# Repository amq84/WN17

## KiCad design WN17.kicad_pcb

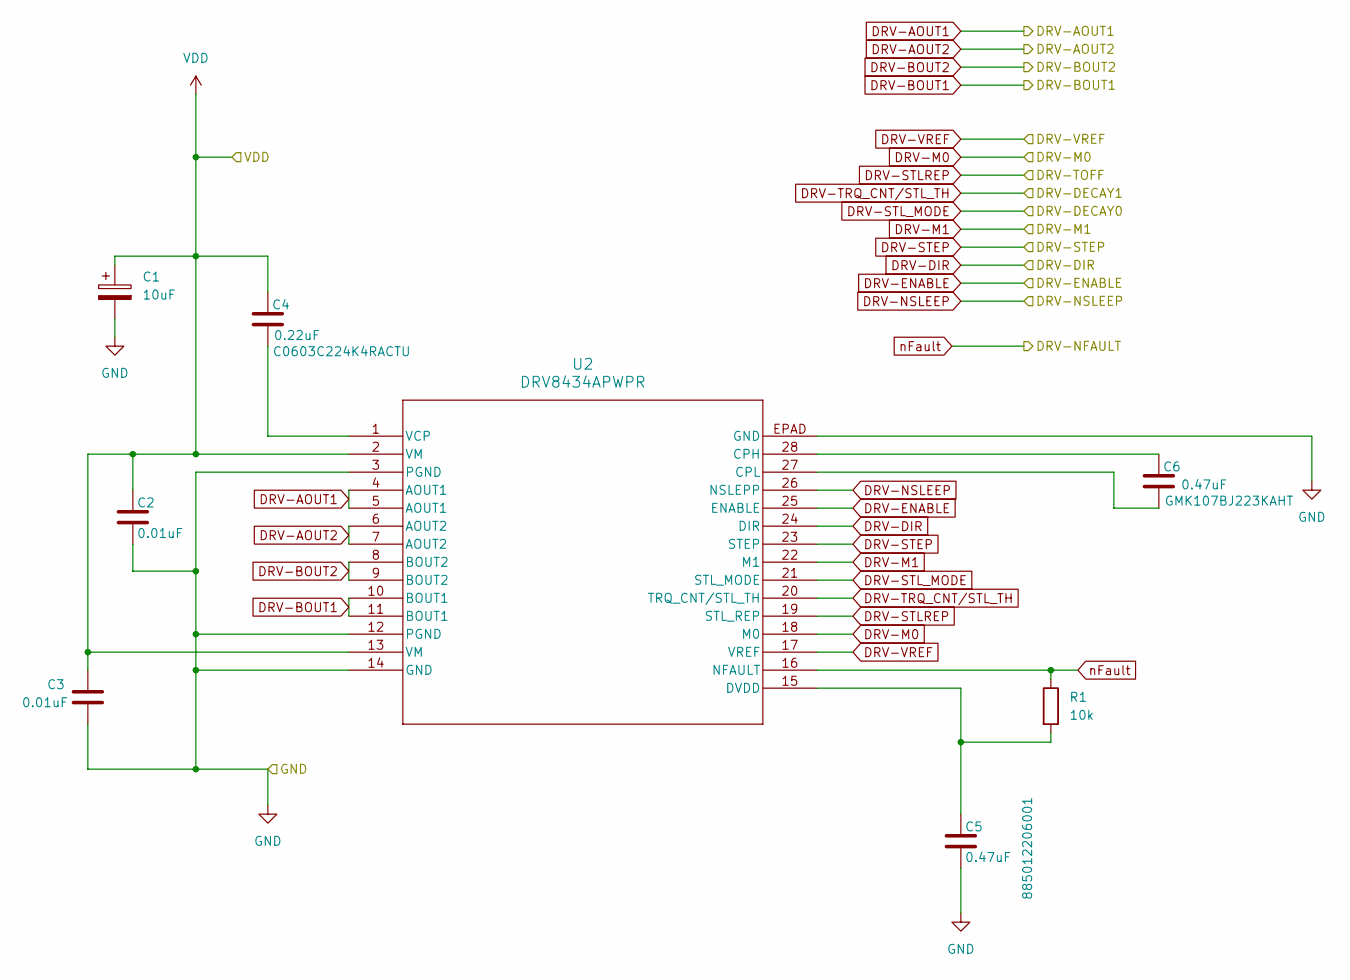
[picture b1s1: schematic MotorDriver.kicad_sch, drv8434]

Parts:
C1: 10uF; CP_Radial_D5.0mm_P2.50mm
C2, C3: 0.01uF; C_0603_1608Metric_Pad1.08x0.95mm_HandSolder
C4: 0.22uF; C_0603_1608Metric_Pad1.08x0.95mm_HandSolder
C5, C6: 0.47uF; C_0603_1608Metric_Pad1.08x0.95mm_HandSolder
R1: 10k; R_0603_1608Metric_Pad0.98x0.95mm_HandSolder
U2: DRV8434APWPR; DRV8434APWPR_TEX

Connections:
DRV-AOUT1: U2.4 (AOUT1), U2.5 (AOUT1); also elsewhere on the board
DRV-AOUT2: U2.6 (AOUT2), U2.7 (AOUT2); also elsewhere on the board
DRV-BOUT1: U2.10 (BOUT1), U2.11 (BOUT1); also elsewhere on the board
DRV-BOUT2: U2.8 (BOUT2), U2.9 (BOUT2); also elsewhere on the board
DRV-DIR: U2.24 (DIR); also elsewhere on the board
DRV-ENABLE: U2.25 (ENABLE); also elsewhere on the board
DRV-M0: U2.18 (M0); also elsewhere on the board
DRV-M1: U2.22 (M1); also elsewhere on the board
DRV-NSLEEP: U2.26 (NSLEPP); also elsewhere on the board
DRV-STEP: U2.23 (STEP); also elsewhere on the board
DRV-STLREP: U2.19 (STL_REP)
DRV-STL_MODE: U2.21 (STL_MODE)
DRV-TRQ_CNT/STL_TH: U2.20 (TRQ_CNT/STL_TH)
DRV-VREF: U2.17 (VREF); also elsewhere on the board
GND: C1.2, C2.2, C3.2, C5.2, U2.3 (PGND), U2.12 (PGND), U2.14 (GND), U2.EPAD (GND); also elsewhere on the board
unnamed: C6.1, U2.28 (CPH)
unnamed: C6.2, U2.27 (CPL)
unnamed: C5.1, R1.2, U2.15 (DVDD)
unnamed: C4.2, U2.1 (VCP)
VDD: C1.1, C2.1, C3.1, C4.1, U2.2 (VM), U2.13 (VM); also elsewhere on the board
nFault: R1.1, U2.16 (NFAULT); also elsewhere on the board

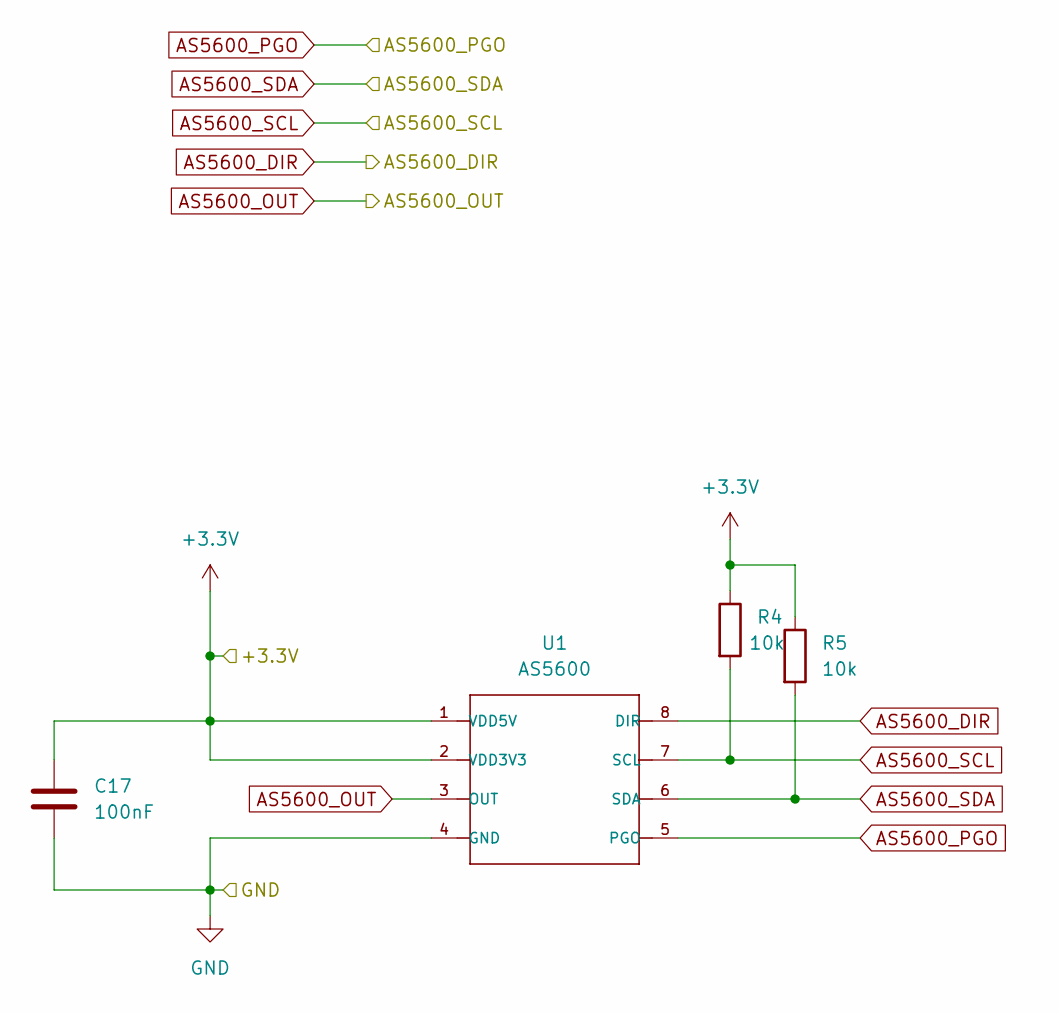
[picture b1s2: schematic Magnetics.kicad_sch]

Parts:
C17: 100nF; C_0603_1608Metric_Pad1.08x0.95mm_HandSolder
R4, R5: 10k; R_0603_1608Metric_Pad0.98x0.95mm_HandSolder
U1: AS5600

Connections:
+3.3V: C17.1, R4.1, R5.1, U1.1 (VDD5V), U1.2 (VDD3V3); also elsewhere on the board
AS5600_DIR: U1.8 (DIR); also elsewhere on the board
AS5600_OUT: U1.3 (OUT); also elsewhere on the board
AS5600_PGO: U1.5 (PGO); also elsewhere on the board
AS5600_SCL: R4.2, U1.7 (SCL); also elsewhere on the board
AS5600_SDA: R5.2, U1.6 (SDA); also elsewhere on the board
GND: C17.2, U1.4 (GND); also elsewhere on the board

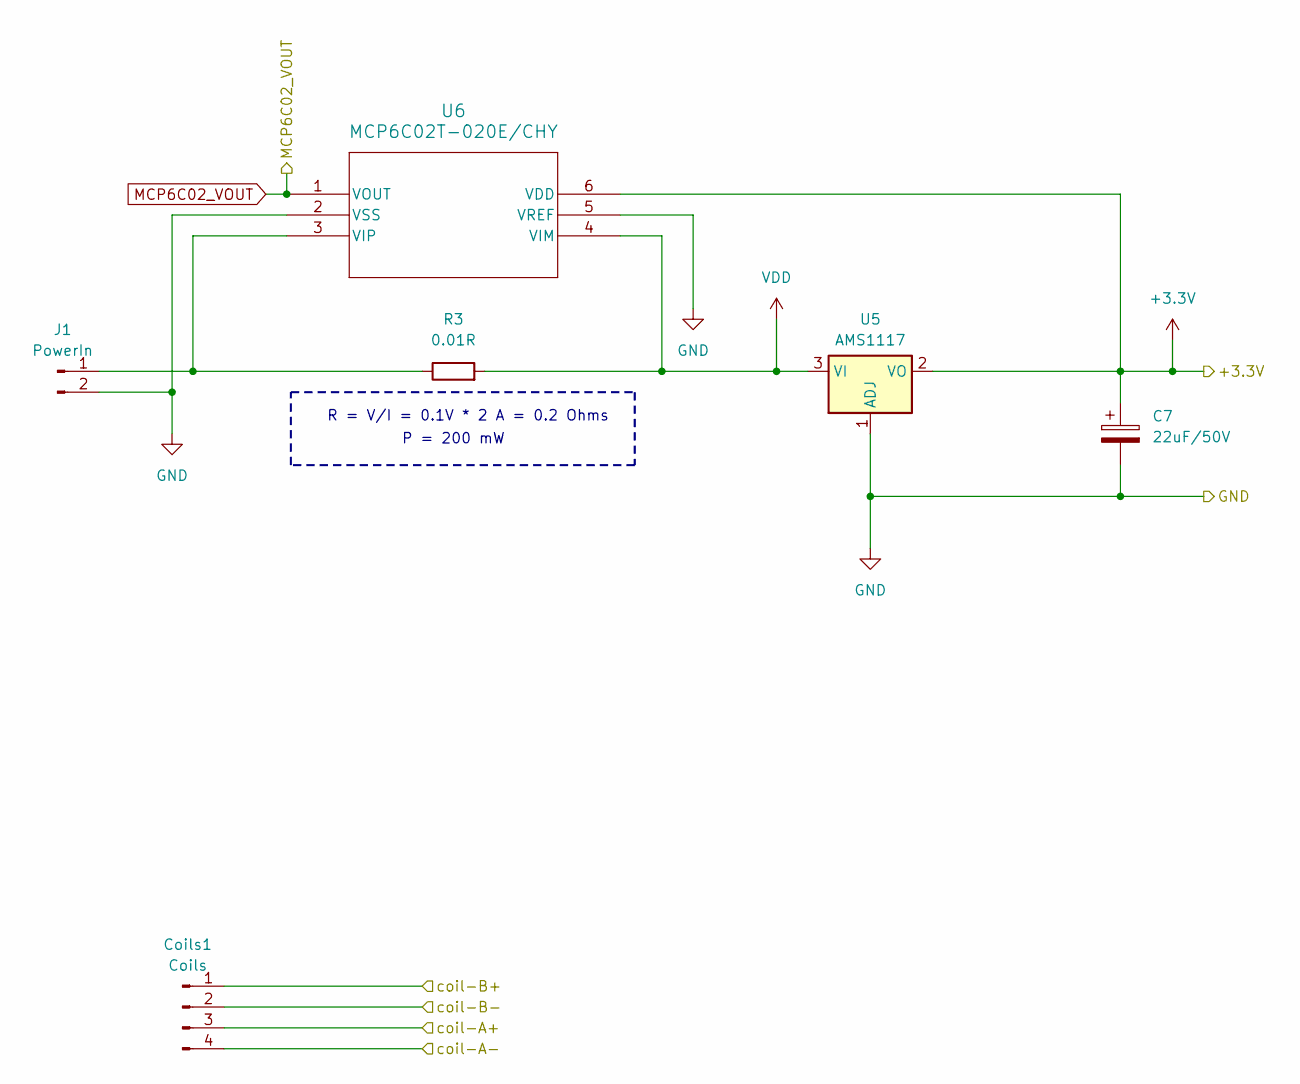
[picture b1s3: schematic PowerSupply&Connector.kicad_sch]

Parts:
C7: 22uF/50V; CP_Radial_D5.0mm_P2.50mm
Coils1: Coils; PinHeader_1x04_P2.54mm_Vertical
J1: PowerIn; PinHeader_1x02_P2.54mm_Vertical
R3: 0.01R; R_1206_3216Metric_Pad1.30x1.75mm_HandSolder
U5: AMS1117; SOT-223-3_TabPin2
U6: MCP6C02T-020E/CHY; SOT-23-6_CHY_MCH

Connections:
+3.3V: C7.1, U5.2 (VO), U6.6 (VDD); also elsewhere on the board
DRV-AOUT1: Coils1.4; also elsewhere on the board
DRV-AOUT2: Coils1.3; also elsewhere on the board
DRV-BOUT1: Coils1.1; also elsewhere on the board
DRV-BOUT2: Coils1.2; also elsewhere on the board
GND: C7.2, J1.2, U5.1 (ADJ), U6.2 (VSS), U6.5 (VREF); also elsewhere on the board
MCP6C02_VOUT: U6.1 (VOUT); also elsewhere on the board
unnamed: J1.1, R3.1, U6.3 (VIP)
VDD: R3.2, U5.3 (VI), U6.4 (VIM); also elsewhere on the board

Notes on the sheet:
R = V/I = 0.1V * 2 A = 0.2 Ohms
P = 200 mW

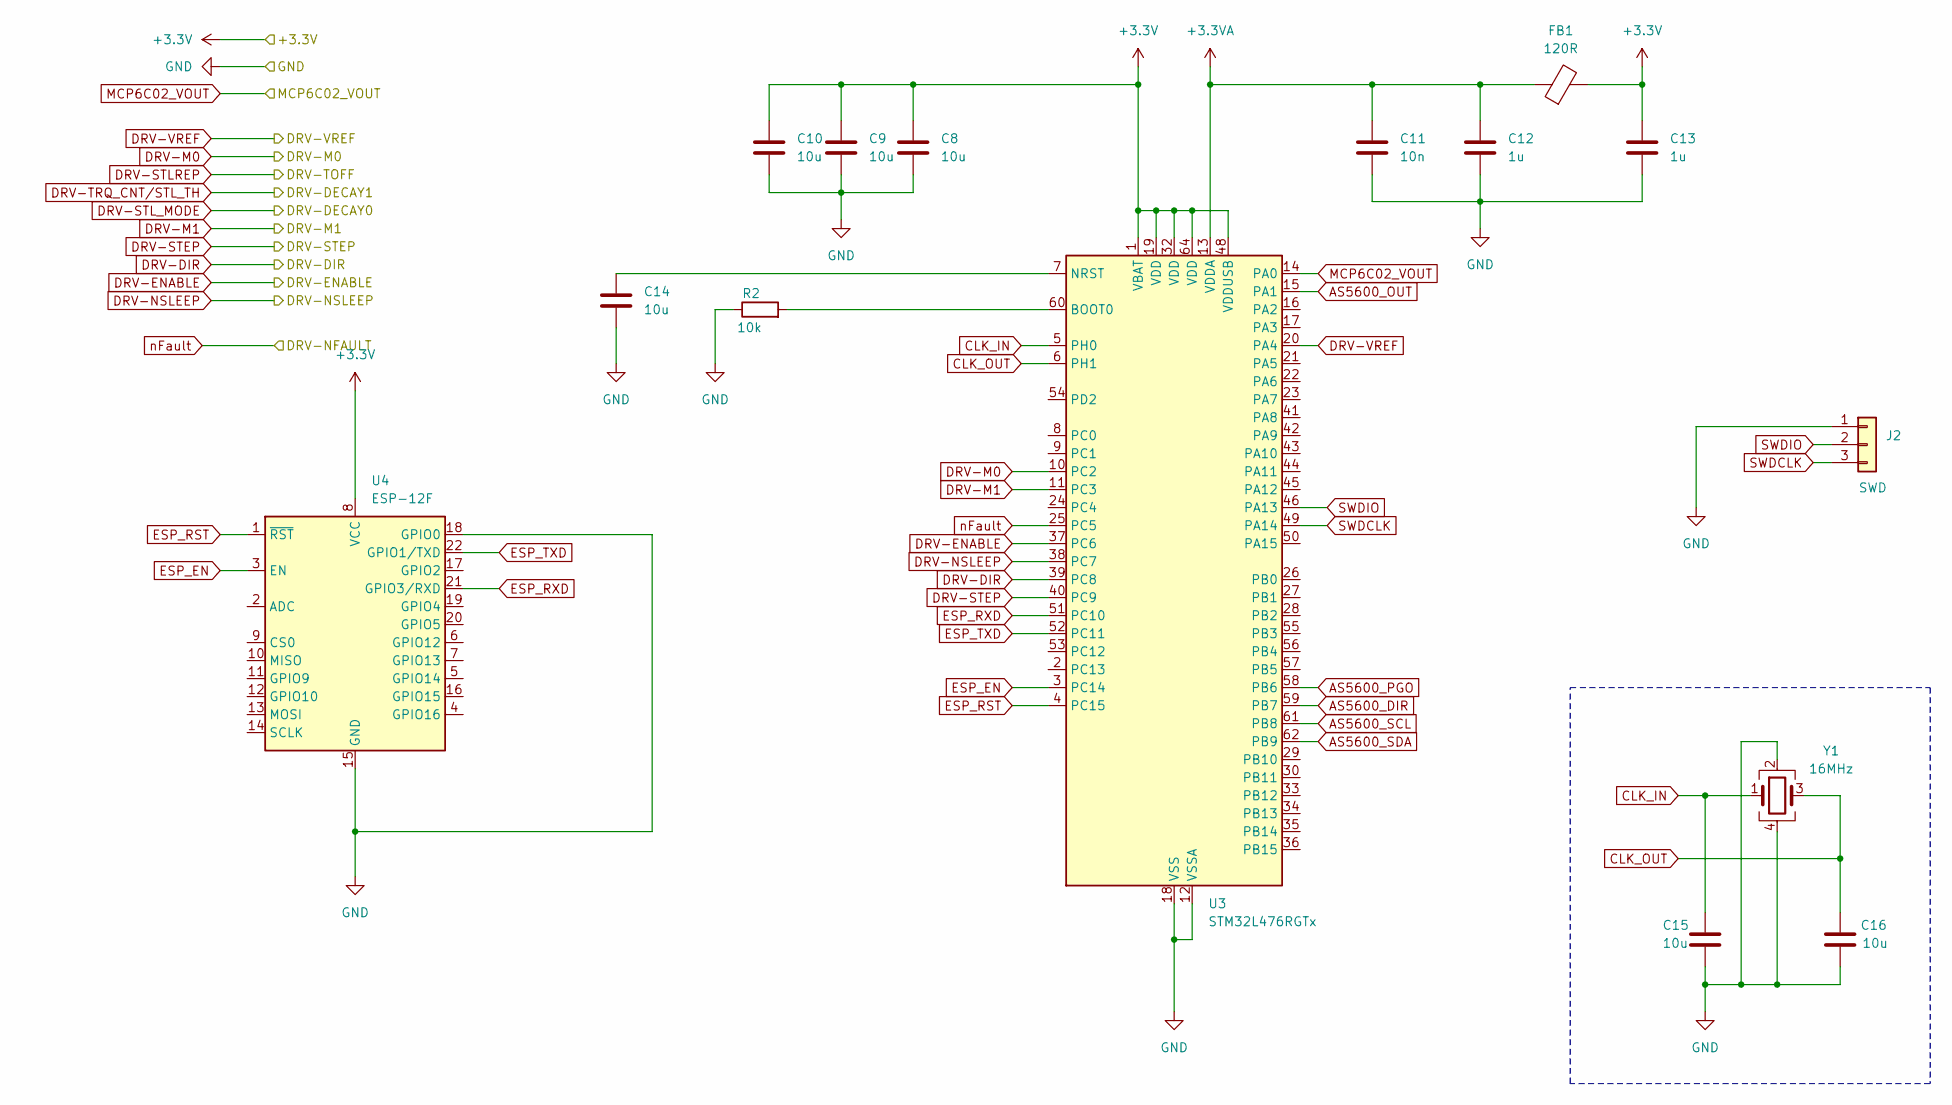
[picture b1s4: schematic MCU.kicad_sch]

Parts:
C8, C9, C10, C14, C15, C16: 10u; C_0603_1608Metric_Pad1.08x0.95mm_HandSolder
C11: 10n; C_0603_1608Metric_Pad1.08x0.95mm_HandSolder
C12, C13: 1u; C_0603_1608Metric_Pad1.08x0.95mm_HandSolder
FB1: 120R; L_0603_1608Metric_Pad1.05x0.95mm_HandSolder
J2: SWD; PinHeader_1x03_P1.00mm_Vertical
R2: 10k; R_0603_1608Metric_Pad0.98x0.95mm_HandSolder
U3: STM32L476RGTx; LQFP-64_10x10mm_P0.5mm
U4: ESP-12F; ESP-12E
Y1: 16MHz; Crystal_SMD_3225-4Pin_3.2x2.5mm_HandSoldering

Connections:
+3.3V: C8.1, C9.1, C10.1, C13.1, FB1.2, U3.1 (VBAT), U3.19 (VDD), U3.32 (VDD), U3.48 (VDDUSB), U3.64 (VDD), U4.8 (VCC); also elsewhere on the board
+3.3VA: C11.1, C12.1, FB1.1, U3.13 (VDDA)
AS5600_DIR: U3.59 (PB7); also elsewhere on the board
AS5600_OUT: U3.15 (PA1); also elsewhere on the board
AS5600_PGO: U3.58 (PB6); also elsewhere on the board
AS5600_SCL: U3.61 (PB8); also elsewhere on the board
AS5600_SDA: U3.62 (PB9); also elsewhere on the board
CLK_IN: C15.1, U3.5 (PH0), Y1.1
CLK_OUT: C16.1, U3.6 (PH1), Y1.3
DRV-DIR: U3.39 (PC8); also elsewhere on the board
DRV-ENABLE: U3.37 (PC6); also elsewhere on the board
DRV-M0: U3.10 (PC2); also elsewhere on the board
DRV-M1: U3.11 (PC3); also elsewhere on the board
DRV-NSLEEP: U3.38 (PC7); also elsewhere on the board
DRV-STEP: U3.40 (PC9); also elsewhere on the board
DRV-VREF: U3.20 (PA4); also elsewhere on the board
ESP_EN: U3.3 (PC14), U4.3 (EN)
ESP_RST: U3.4 (PC15), U4.1 (~RST)
ESP_RXD: U3.51 (PC10), U4.21 (GPIO3/RXD)
ESP_TXD: U3.52 (PC11), U4.22 (GPIO1/TXD)
GND: C8.2, C9.2, C10.2, C11.2, C12.2, C13.2, C14.2, C15.2, C16.2, J2.1, R2.1, U3.12 (VSSA), U3.18 (VSS), U3.31 (VSS), U3.47 (VSS), U3.63 (VSS), U4.15 (GND), U4.18 (GPIO0), Y1.2, Y1.4; also elsewhere on the board
MCP6C02_VOUT: U3.14 (PA0); also elsewhere on the board
unnamed: R2.2, U3.60 (BOOT0)
unnamed: C14.1, U3.7 (NRST)
SWDCLK: J2.3, U3.49 (PA14)
SWDIO: J2.2, U3.46 (PA13)
nFault: U3.25 (PC5); also elsewhere on the board

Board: 2 copper layers, 33 parts (2 on the bottom side), 37 nets, no tracks yet.

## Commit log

2024-05-19 Added Motor driver capacitors and supply
2024-05-20 Etiquetas y pines modulo driver
2024-05-20 Moved driver to better position
2024-05-20 Finished motor driver
2024-05-20 cajetin motor driver actualizado
2024-05-20 Ordered coils
2024-05-21 Clock
2024-05-22 Schematic done
